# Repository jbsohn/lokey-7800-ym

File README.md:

# Lokey 7800 YM

> **Status:** v0.2 PCBs have been sent to the manufacturer — prototype boards are pending, and we're working on hardware validation.

## Project Overview

The Atari 7800 community's favorite audio upgrades have a supply problem: POKEY clones run **~$10-$40 each — when they're in stock** — and the YM2151 has been out of production for decades, commanding collector prices used. The **Lokey 7800 YM** takes a different route: the **YM2149 PSG** — the Atari ST's sound chip — is still manufactured today as the **KC89C72** clone for **about $2**. One in-production chip brings three-channel sound to the 7800, and with it a direct bridge to four decades of Atari ST music and a tracker ecosystem that is still alive and composing. Original YM2149 chips are also plentiful as used or New-Old-Stock (NOS) parts.

### What's in a Name?

The **Lokey** name is a triple-layered nod to the project's roots:

- **POKEY**: A respectful "cousin" to Atari’s legendary sound chip.
- **Low-Key**: Reflecting our philosophy of a minimalist, stealthy, and cost-effective design.
- **Loki**: Inspired by the Norse god of mischief—bringing a bit of technical "trickery" to the Atari 7800 bus.

The project views the **Atari ST** as a potential **Creation System**.
With established trackers (like Protracker ST or Maxymiser), it offers a path for audio production. Modern cross-platform tools like [**Furnace Tracker**](https://tildearrow.org/furnace) and [**Arkos Tracker**](https://www.julien-nevo.com/arkostracker/) (which is dedicated specifically to the AY/YM architecture) can also export VGM data for use with our tools on the 7800.

The **Atari 7800** acts as the **Consumer** of these assets. By bridging the hardware gap, we hope to allow the 7800 to play music from the ST era or new compositions from modern trackers.

### Design Goals

- **In-Production Parts Only**: No POKEY or YM2151 unobtainium, and no expensive FPGAs. Every part on the BOM should be sourceable new today (e.g. the KC89C72 YM2149 clone).
- **No SMD**: Hand-solderable through-hole components only, so hobbyists without a hot air rework station can build and repair boards.
- **Low Cost**: Keep the total build cost minimal.
- **Time-Period Accurate**: Stay faithful to what would have been technically feasible/authentic to the Atari 7800/ST era, rather than leaning on modern shortcuts.

### Hardware & Development Status

- **Working Prototype**: We have a hand-built cartridge prototype that has been verified to work.
- **PCB Effort**: We are working on a PCB design using a code-to-PCB workflow (**tscircuit**).
- **Reproducible Hardware Builds**: GitHub Actions rebuilds the PLD logic and both PCBs from source on every push. You can also build locally using the preconfigured **Docker Dev Container** (currently supported for building and routing PCBs).
- **Conversion Tools**: The project includes experimental tools to convert music files. The current C# implementation was a temporary hack to parse ST captures; this will be rewritten in C++ and optimized to support simultaneous music and sound effects playback.
- **SDK Progress**: We are working toward a set of tools and drivers to help others add YM music to their 7800 projects.
- **Custom Emulation**: For testing without hardware, we use forks of **a7800** and **js7800** that implement this specific memory mapping. _If this project gains momentum, we hope these changes might eventually be useful to the official upstream projects._

## Status: STABLE ALPHA

We have achieved playback on physical Atari 7800 consoles using a bitmask-compressed register engine. The current implementation is designed to be efficient, leaving significant CPU time for other tasks.

## See it in Action

### Hardware Prototype

### Web Emulator (Instant Play)

Test the bridge right now in your browser using our custom **js7800** fork.
👉 **[Play the YM2149 Demos in your Browser](https://jbsohn.github.io/js7800-ym-player/)**

### Real Hardware (ANCOOL1 Stress Test)

This video shows a physical Atari 7800 playing a full 92-second capture of the "ANCOOL1" track, filling 96% of a single 32KB ROM bank to prove bus stability and engine efficiency.

## Documentation

- **[Development Guide](CLAUDE.md)** - Technical standards and build process for contributors and AI assistants.
- **[AI Development Agents](AGENTS.md)** - Specialized instructions for AI-assisted development and automation.
- **[SDK Samples & Building](docs/Samples.md)** - Compile ROMs and set up the environment.

- **[File Extension Reference](docs/FileExtensions.md)** - Guide to `.ymb`, `.ymi`, `.rom`, and `.a78` files.
- **[Hardware & Wiring](docs/Hardware.md)** - Shared memory mapping and connector/chip pinouts.
  - **[28-Pin Board](docs/Hardware-28pin.md)** - Single-YM2149, jumper-configured ROM board.
  - **[32-Pin Board](docs/Hardware-32pin.md)** - Bank-switched ROM board (fixed 32KB code + 16KB YM-IOA banked data window, 128KB-256KB) (Experimental Pre-Alpha v0.2 - Untested).

- **[PCB Design (tscircuit)](docs/PCB.md)** - Code-to-PCB workflow.

- **[Emulator Support](docs/Emulation.md)** - Using `a7800` and `js7800` for development.

- **[Toolchain & Diagnostics](docs/Tools.md)** - Register conversion (`YmToYmb`, `VgmToYmb`), audio verification (`YmbToWav`), and hardware signal verification.
- **[YMB Format](docs/YmbFormat.md)** - Technical specification of the music binary format.
- **[Musical Credits](docs/Musicians.md)** - Honoring the original composers.
- **[TODO](docs/TODO.md)** - Known issues and improvements.
- **[Future Ideas](docs/FutureIdeas.md)** - Roadmap for hardware/software expansions.

---

## Technical Highlights

- **Hardware**: Uses **YM2149 PSG** mapped to `$0800`/`$0801` (Pokey800-compatible).
- **Compression**: Multi-stage **Pattern-Based Delta Masking** for maximum ROM efficiency.
- **Timing**: Automatic **Pitch Scaling** (1.79MHz vs 2.0MHz) ensures tracks stay in tune.
- **Diagnostics**: Built-in **Software Triad** visualizer for bare-metal debugging.

## Acknowledgements & Credits

- **Karri Kaksonen (karrika)**: For the excellent [Otaku-flash](https://github.com/karrika/Otaku-flash) project. We have integrated the **Stable Alpha** Atari 7800 cartridge footprints, symbols, and professional design rules from this MIT-licensed repository.
- **Simon Frankau ([galette](https://github.com/simon-frankau/galette))**: For the open-source **galette** logic assembler. It provides a modern, cross-platform toolchain for compiling ATF16V8B/ATF22V10 logic, saving us from the legacy Windows tools.
- **Dan Boris (AtariHQ)**: For the indispensable [7800 Cartridge Technical Specifications](https://atarihq.com/danb/7800cart/a7800cart.shtml) and reference diagrams that made this hardware mapping possible.
- **Olivier PONCET (aym-js)**: For the excellent, high-fidelity [aym-js](https://github.com/ponceto/aym-js) YM2149/AY-3-8910 emulator core. Its tone/noise/envelope generator model and DAC tables underpin `tools-cs/Core/AymEmulator.cs` (a literal C# port), which powers `YmbToWav`'s audio verification and has since been ported a second time into Go to give the `test7800` emulator fork native YM2149 support. A small, focused piece of GPL-licensed JavaScript that ended up doing a lot of work across this project — thank you!

- **Arnaud Carré (Leonard/OXG)**: For the excellent [StSound](https://github.com/arnaud-carre/StSound) project. The melodic assets used for hardware testing were sourced via this project's research.

- **Eagle & Ecernosoft**: For the insightful ideas and technical tips provided on the forums, including the Pokey800 mapping recommendation and the inspiration for the "Active Shunt" audio stage design.

- **Original Musicians & Composers**: For the timeless tracks used as benchmarks for this project. See **[Musical Credits](docs/Musicians.md)** for a full list of artists.

- **The Atari Community**: We are grateful to the dedicated fans keeping the 16-bit and 8-bit flames alive through archival and homebrew development.

## Contributing

This project is completely open source, and since this is a first-time PCB design, community feedback and contributions are highly welcome! _"Help! I need someone... not just anybody... you know I need someone!"_ as the Beatles said, so any help or review of the schematics, code, or board layout is greatly appreciated.

## AI Assistance

This project was developed with assistance from AI. For the author, AI has been a "force multiplier"—making it possible to tackle long-held "I've always wanted to do this" projects within the limited hours of evenings and weekends. In particular, it really helped with developing the [route_and_patch.py](file:///home/john/Projects/7800-ym2149-lab/pcb/route_and_patch.py) build pipeline.

For reflections on the legacy of the Atari ST and how AI is changing the landscape of hardware and software side-projects, see the author's blog posts:

[John's Music & Tech](https://johnsmusicandtech.com/)

## License

This repository is dual-licensed:

- **MIT License**: Applies to the 6502 target code ([examples/](file:///home/john/Projects/7800-ym2149-lab/examples) and [include/](file:///home/john/Projects/7800-ym2149-lab/include)). You can use, modify, and distribute this code in your homebrew games without any requirement to open-source your game. See [examples/LICENSE](file:///home/john/Projects/7800-ym2149-lab/examples/LICENSE) and [include/LICENSE](file:///home/john/Projects/7800-ym2149-lab/include/LICENSE).
- **GPL-2.0**: Applies to the host tools ([tools-cs/](file:///home/john/Projects/7800-ym2149-lab/tools-cs)), hardware layouts ([pcb/](file:///home/john/Projects/7800-ym2149-lab/pcb)), PLD logic ([pld/](file:///home/john/Projects/7800-ym2149-lab/pld)), and documentation. Modifying and redistributing these requires sharing your changes. Using these tools to build your ROM does not make your game GPL. See [LICENSE](file:///home/john/Projects/7800-ym2149-lab/LICENSE).

### Why the split?
The emulation core ([AymEmulator.cs](file:///home/john/Projects/7800-ym2149-lab/tools-cs/Core/AymEmulator.cs)) is a C# port of Olivier Poncet's GPL-licensed **aym-js**, requiring GPL compatibility. Since the 6502 code shipped on the cartridge does not link or interact with the host emulator code, it remains under the permissive MIT license.

**Disclaimer:** Use at your own risk. The author is not responsible for hardware damage or data loss.

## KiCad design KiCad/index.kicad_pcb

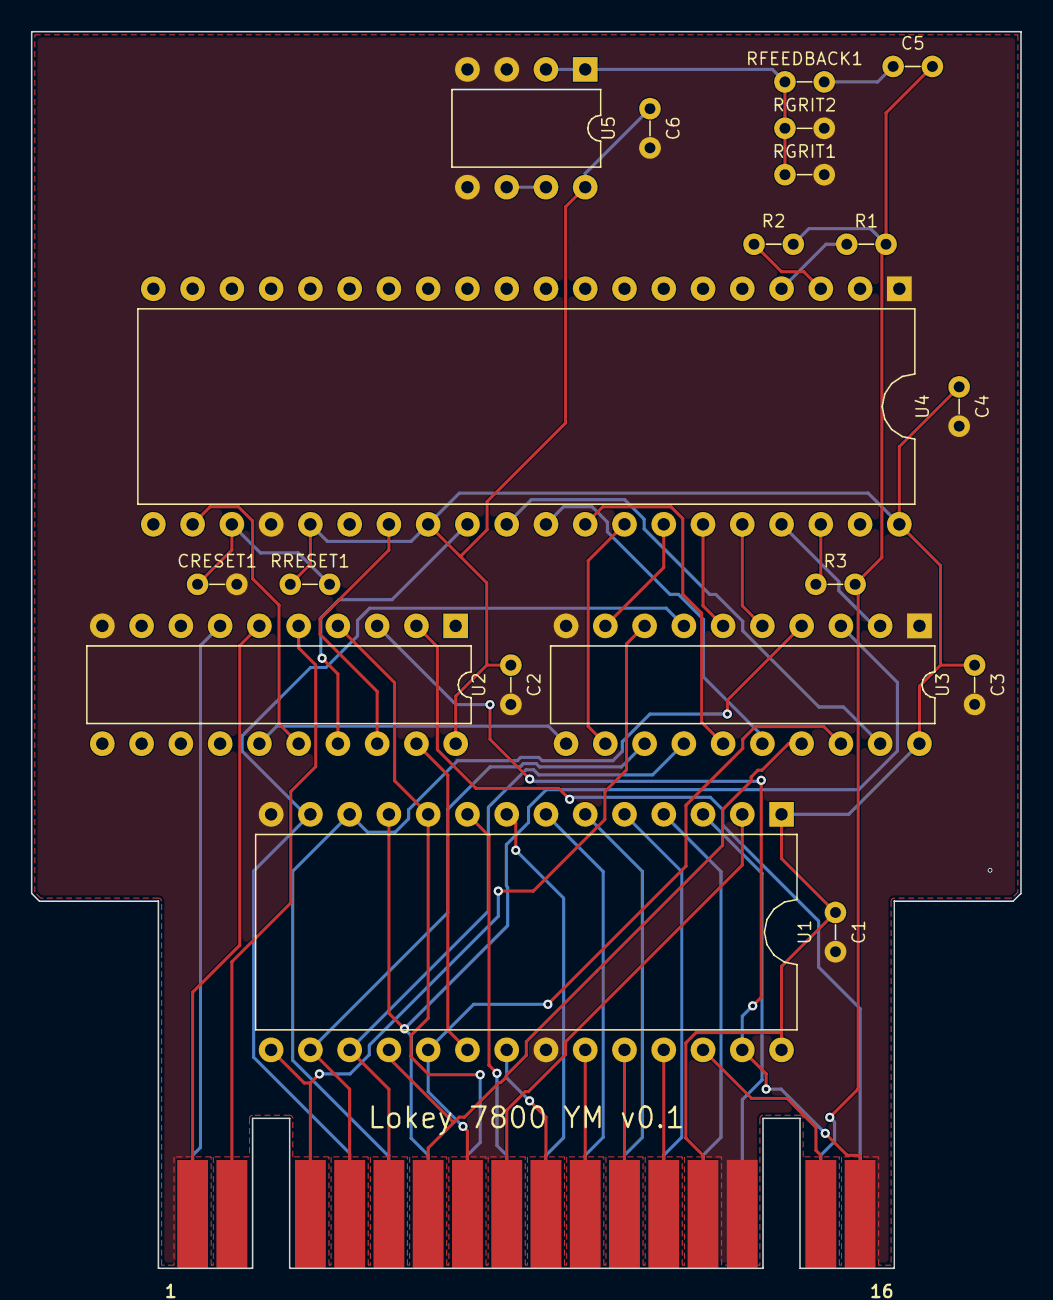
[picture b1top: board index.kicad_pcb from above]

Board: 2 copper layers, 64.0 x 80.0 mm, 20 parts (0 on the bottom side), 50 nets.

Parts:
C1, C2, C3, C4, C6: 0.1uF; capacitor_axial
C5: 10uF; capacitor_axial
CRESET1: 10uF; capacitor_axial
J1: chip
R1, R2, R3: 1kΩ; resistor_axial
RFEEDBACK1: 4.7kΩ; resistor_axial
RGRIT1, RGRIT2: 4.7kΩ; resistor_axial
RRESET1: 4.7kΩ; resistor_axial
U1: chip_dip28_w600mil
U2, U3: chip_dip20_w300mil
U4: chip_dip40_w600mil
U5: chip_dip8_w300mil

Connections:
A0: J1.26, U1.10, U2.4
A1: J1.25, U1.9
A2: J1.24, U1.8
A3: J1.23, U1.7
A4: J1.22, U1.6
A5: J1.21, U1.5
A6: J1.20, U1.4
A7: J1.19, U1.3
A8: J1.12, U1.25
A9: J1.11, U1.24
A10: J1.9, U1.21
A11: J1.10, U1.23
A12: J1.8, U1.2
A13: J1.15, U1.26
A14: J1.16, U1.27, U2.3
A15: J1.17, U2.2
ANALOG_A: R1.1, U4.4
ANALOG_B: R2.1, U4.3
ANALOG_C: R3.1, U4.38
BC1: U2.17, U4.29
BDIR: U2.18, U4.27
CAP_PLUS: C5.1, RFEEDBACK1.2
D0: J1.27, U1.11, U3.3
D1: J1.28, U1.12, U3.4
D2: J1.29, U1.13, U3.7
D3: J1.3, U1.15, U3.8
D4: J1.4, U1.16, U3.13
D5: J1.5, U1.17, U3.14
D6: J1.6, U1.18, U3.17
D7: J1.7, U1.19, U3.18
DA0: U3.2, U4.37
DA1: U3.5, U4.36
DA2: U3.6, U4.35
DA3: U3.9, U4.34
DA4: U3.12, U4.33
DA5: U3.15, U4.32
DA6: U3.16, U4.31
DA7: U3.19, U4.30
GND: C1.2, C2.2, C3.2, C4.2, C6.2, CRESET1.2, J1.14, J1.30, RGRIT1.2, RGRIT2.2, U1.14, U1.22, U2.10, U3.1, U3.10, U4.1, U4.24, U5.3, U5.4, U5.5
HALT: J1.2, U2.5
OPAMP_FB: RFEEDBACK1.1, RGRIT1.1, RGRIT2.1, U5.1, U5.2
PHI2: J1.32, U2.7
PHI2OUT: U2.16, U4.22
RESET_DELAYED: CRESET1.1, RRESET1.2, U4.23
ROM_CE: U1.20, U2.19
RW: J1.1, U2.6
SUM_NODE: C5.2, J1.18, R1.2, R2.2, R3.2
U5_UNUSED_FB: U5.6, U5.7
VCC: C1.1, C2.1, C3.1, C4.1, C6.1, J1.13, RRESET1.1, U1.1, U1.28, U2.20, U3.20, U4.25, U4.28, U4.40, U5.8
YM_LE: U2.15, U3.11

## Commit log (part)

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2026-02-22 start of GAL code
2026-02-22 update test code for YM, add Makefile, set address to $4000
2026-02-28 move to galette from galasm, add vbi/ym test
2026-03-07 add WinCupl pld for gal
2026-03-08 first win! simple 3 notes played on 7800 and matches our fork of a7800
2026-03-08 fixed vbi sample, remove unused samples
2026-03-08 added a picture of the "lab"
2026-03-08 add more to the readme, taking a short break to decide next steps
2026-03-20 Update build system, replace GAL logic, and add YM music samples.
2026-03-22 update WinCupl gal, add C# tool to to test cart pins not on rom
2026-03-24 document plan for 74HCT373, add Galette pld which hopefully is what we can use instead of WinCupl
2026-03-26 Rename project to Lokey 7800 YM
2026-03-26 add tool to look at gal pins
2026-03-29 start of potential pcb in Python
2026-03-29 update PCB, build, and readme
2026-03-29 update build and readme
2026-03-29 add audio lines, update readme
2026-03-29 update background on schematic SVG
2026-03-29 update readme and schematic svg
2026-03-30 update readme, fix viewing issue in dark mode
2026-03-30 another readme update
2026-03-31 update skidl
2026-04-01 intial trial of tscircuit
2026-04-01 use kicad 9
2026-04-02 rearrange pcb
2026-04-02 adjust pcb layout
2026-04-02 add edge connector notch
2026-04-05 update tscircuit
2026-04-05 use "T" shape, adjust layout
2026-04-05 update tools
2026-04-06 update circuit
2026-04-07 update YM gal
2026-04-07 remove quad writes to YM
2026-04-07 add tool
2026-04-08 switch to galette, update readme
2026-04-08 update readme, graduade project from the lab
2026-04-08 add AY/YM to Hardware Pinout Reference
2026-04-09 fix warnings, clean up tools
2026-04-09 update tsconfig.json for tscircuit
2026-04-09 add tool to convert YM to 7800 bin
2026-04-09 7800 ancool1 conversion from ST
2026-04-09 update readme, add test rom for a7800 emulator
2026-04-10 start tuning YM conversion
2026-04-12 remove unused files
2026-04-12 consolidate high-precision delay logic and optimize ROM layout
2026-04-12 update YmToBin and Makefile
2026-04-14 update YmToBin to C#12, readme.md and docs for YmToBin
2026-04-14 remove "perfect" from readme.md... because it's not LOL
2026-04-14 add note about assembler used
2026-04-14 update readme about AY/YM header for emulators
2026-04-16 add VGM tools, BIN to wav tool, update build system
2026-04-17 update README.md and create/move documentation
2026-04-17 add schematic PDF
2026-04-18 fix 7-Zip detection for macOS compatibility
2026-04-18 begin refactor for expansion
2026-04-18 use correct extension for C# scripts
2026-04-18 sync up AY changes
2026-04-18 cleanup
2026-04-18 move C# scripts to real .NET project
2026-04-18 update some directory names and docs
2026-04-18 recommendations that got missed during GitHub/Gemini code review
2026-04-19 ideas for a YmSound implementation
2026-04-19 limit screen color cycling
2026-04-19 cleanup code and docs
2026-04-19 build AOT apps to bin dir, update Makefile
2026-04-19 fix warning
2026-04-19 fix merge, testing YmSound
2026-04-20 update hardware validation scripts
2026-05-10 update docs and TSCirucit for MVP, updated amp to 7800 audio, document we are using modern ATF instead of GAL
2026-05-10 sync up with prototype
2026-05-10 update markdown
2026-05-16 bug fix in PCB and sample-code
2026-05-16 added experimental ca65 build
2026-05-16 fixes to ca65 versions
2026-05-16 fix merge
2026-05-16 update CA65 build
2026-05-16 Gemini GitHub code review suggestions
2026-05-16 experiment begin with MAD assembler
2026-05-17 cleanup project structure and names
2026-05-17 code cleanup
2026-05-17 set some coding standards for project
2026-05-17 remove ca65/mads sub projects
2026-06-02 testing
2026-06-03 cleanup schematic
2026-06-04 rework PCB
2026-06-05 add clearer nodes about op-amp and YM power on reset
2026-06-07 update PCB
2026-06-07 update schematic
2026-06-08 update PCB, add exported KiCad project
2026-06-11 update schematics and KiCad
2026-06-14 update alignment
2026-06-14 update opamp
2026-06-14 update amp layout
2026-06-15 update PCB build process
2026-06-15 update .gitignore items
2026-06-15 move patch for pcb to pcb subproject
2026-06-15 update gerbers
2026-06-15 small update to PCB and add TODO.md
2026-06-16 cleanup pcb build
2026-06-16 add previews and schematic to Makefile
2026-06-16 fix opamp setting to match prototype
2026-06-16 cleanup and optimize pcb build, setup for macOS
2026-06-17 reorg pcb, add clean
2026-06-17 updates to docs
2026-06-17 add PCB warning
2026-06-18 start of expansion to 16k and 64k 28 pin ROMs
2026-06-18 update make pcb path
2026-06-19 update PCB, move text
2026-06-21 add error checking to route script
2026-06-21 clarify license
2026-06-23 update cart outline to fit cartridge case, update documents to outline where we are taking this
2026-06-24 attempt new layout
2026-06-25 add YM2
2026-06-26 start of support for 32-pin ROM
2026-06-27 update PCB and hardware doc
2026-06-27 add SRAM
2026-06-28 update PCB for 28pin 16k, 32k, 64k rom
2026-06-28 use consistent values for pcb x and y
2026-06-28 remove commented out code
2026-06-29 reorg project, add GitHub workflows
2026-06-29 update Docker image
2026-06-29 update yml
2026-06-29 update freerouting
2026-06-29 update freerouting jar
2026-06-29 install make
2026-06-29 install bun
2026-06-29 install JDK 25
2026-06-29 attempt to remove freerouting warning
